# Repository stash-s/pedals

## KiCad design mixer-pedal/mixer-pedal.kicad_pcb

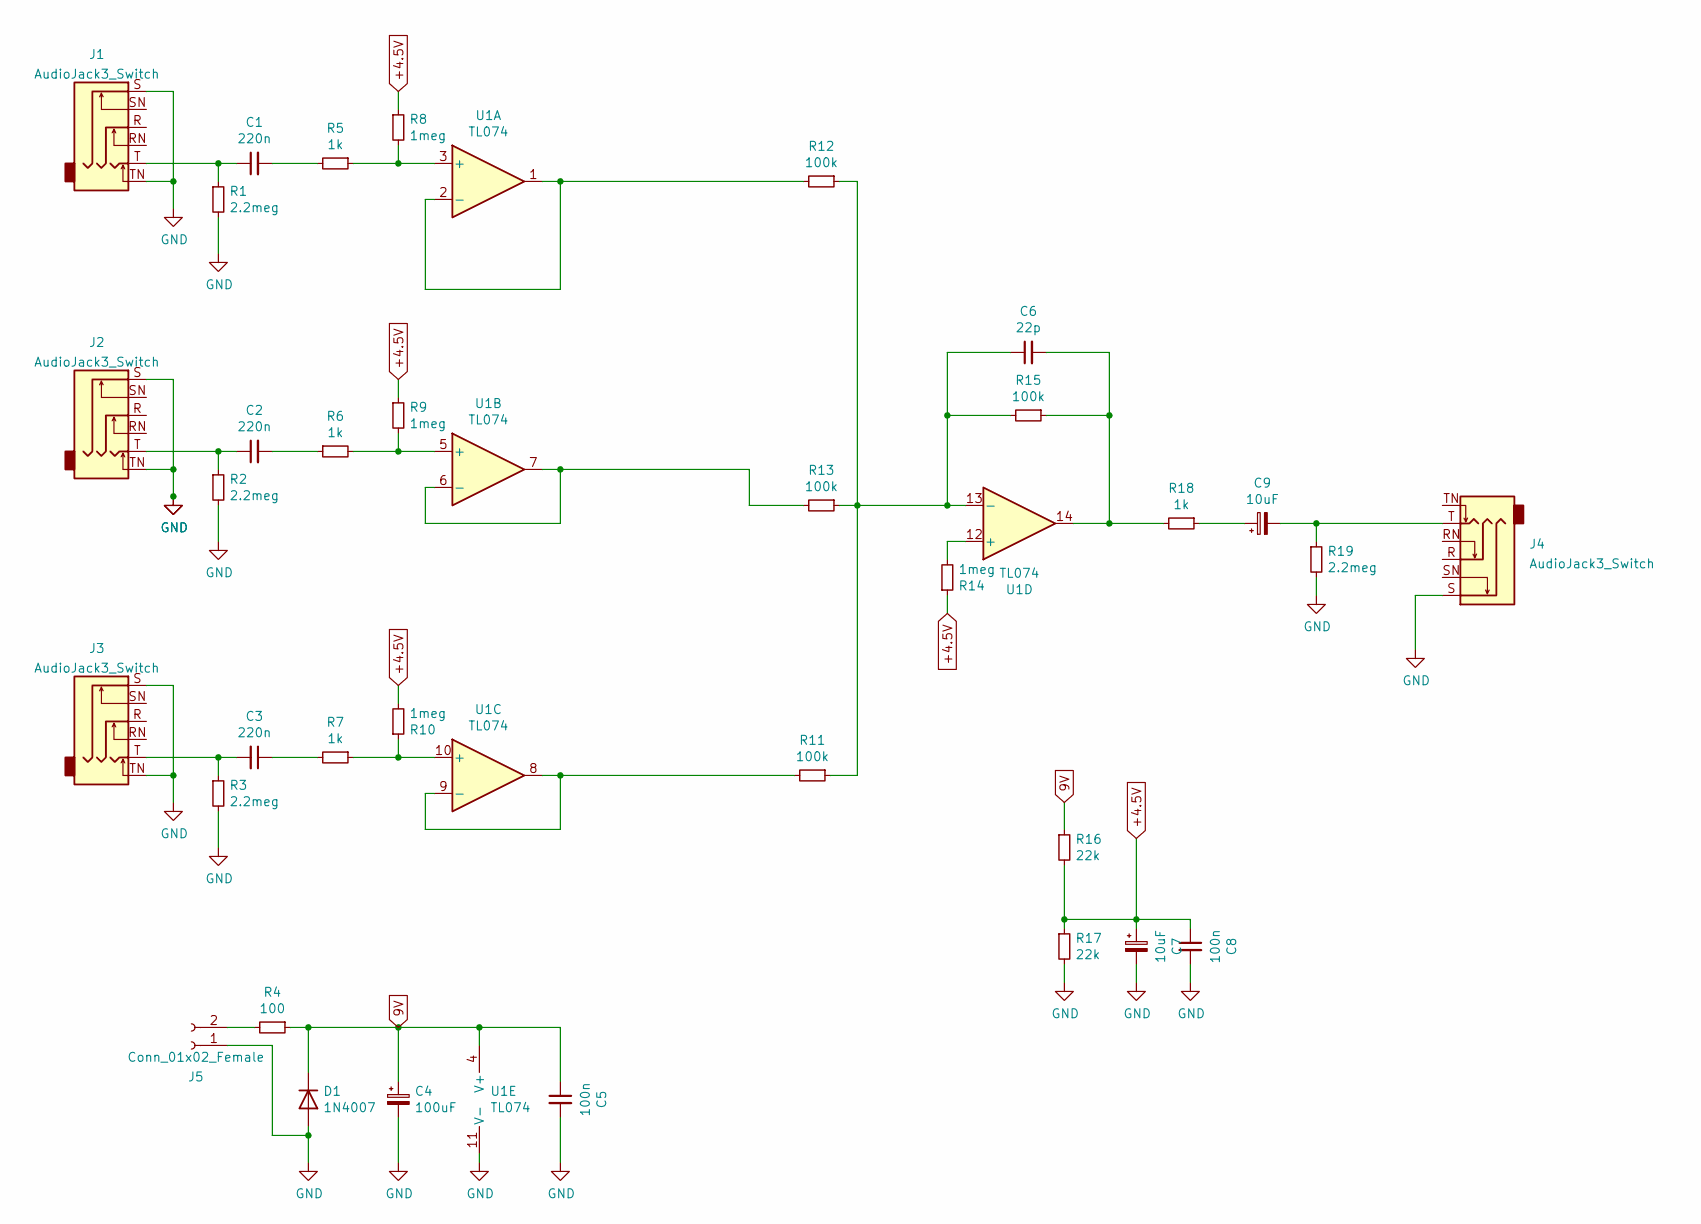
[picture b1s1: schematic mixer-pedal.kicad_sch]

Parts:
C1, C2, C3: 220n; C_Rect_L7.0mm_W2.5mm_P5.00mm
C4: 100uF; CP_Radial_D10.0mm_P5.00mm
C5, C8: 100n; C_Rect_L7.0mm_W2.5mm_P5.00mm
C6: 22p; C_Rect_L7.0mm_W2.5mm_P5.00mm
C7, C9: 10uF; CP_Radial_D10.0mm_P5.00mm
D1: 1N4007; D_DO-41_SOD81_P10.16mm_Horizontal
J1, J2, J3, J4: AudioJack3_Switch; Jack_6.35mm_Rean_NYS215_Horizontal
J5: Conn_01x02_Female; SolderWire-0.5sqmm_1x02_P4.6mm_D0.9mm_OD2.1mm_Relief
R1, R2, R3, R19: 2.2meg; R_Axial_DIN0207_L6.3mm_D2.5mm_P7.62mm_Horizontal
R4: 100; R_Axial_DIN0207_L6.3mm_D2.5mm_P7.62mm_Horizontal
R5, R6, R7, R18: 1k; R_Axial_DIN0207_L6.3mm_D2.5mm_P7.62mm_Horizontal
R8, R9, R10, R14: 1meg; R_Axial_DIN0207_L6.3mm_D2.5mm_P7.62mm_Horizontal
R11, R12, R13, R15: 100k; R_Axial_DIN0207_L6.3mm_D2.5mm_P7.62mm_Horizontal
R16, R17: 22k; R_Axial_DIN0207_L6.3mm_D2.5mm_P7.62mm_Horizontal
U1: TL074; DIP-14_W7.62mm_Socket_LongPads

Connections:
9V: C4.1, C5.1, D1.1 (K), R4.1, R16.1, U1.4 (V+)
+4.5V: C7.1, C8.1, R8.1, R9.1, R10.2, R14.1, R16.2, R17.1
GND: C4.2, C5.2, C7.2, C8.2, D1.2 (A), J1.S, J1.TN, J2.S, J2.TN, J3.S, J3.TN, J4.S, J5.1, R1.2, R2.2, R3.2, R17.2, R19.2, U1.11 (V-)
unnamed: C1.1, J1.T, R1.1
unnamed: C1.2, R5.2
unnamed: C2.1, J2.T, R2.1
unnamed: C2.2, R6.1
unnamed: C3.1, R7.2
unnamed: C3.2, J3.T, R3.1
unnamed: C6.1, R11.1, R12.1, R13.1, R15.2, U1.13 (-)
unnamed: C6.2, R15.1, R18.2, U1.14
unnamed: C9.1, R18.1
unnamed: C9.2, J4.T, R19.1
unnamed: J5.2, R4.2
unnamed: R5.1, R8.2, U1.3 (+)
unnamed: R6.2, R9.2, U1.5 (+)
unnamed: R7.1, R10.1, U1.10 (+)
unnamed: R11.2, U1.8, U1.9 (-)
unnamed: R12.2, U1.1, U1.2 (-)
unnamed: R13.2, U1.6 (-), U1.7
unnamed: R14.2, U1.12 (+)

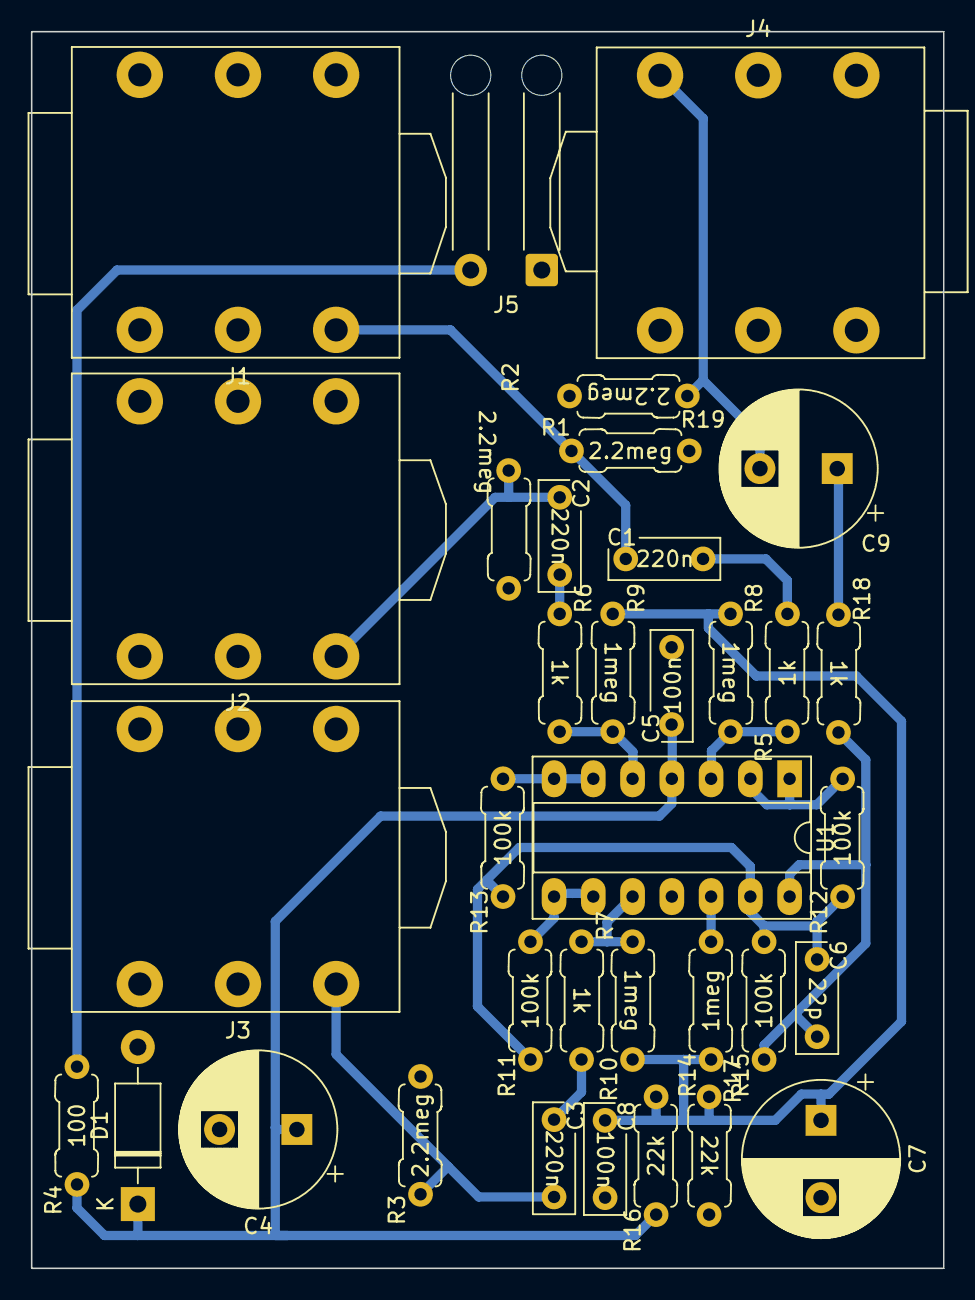
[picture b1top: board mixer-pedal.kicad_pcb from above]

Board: 2 copper layers, 59.0 x 80.0 mm, 35 parts (0 on the bottom side), 21 nets.

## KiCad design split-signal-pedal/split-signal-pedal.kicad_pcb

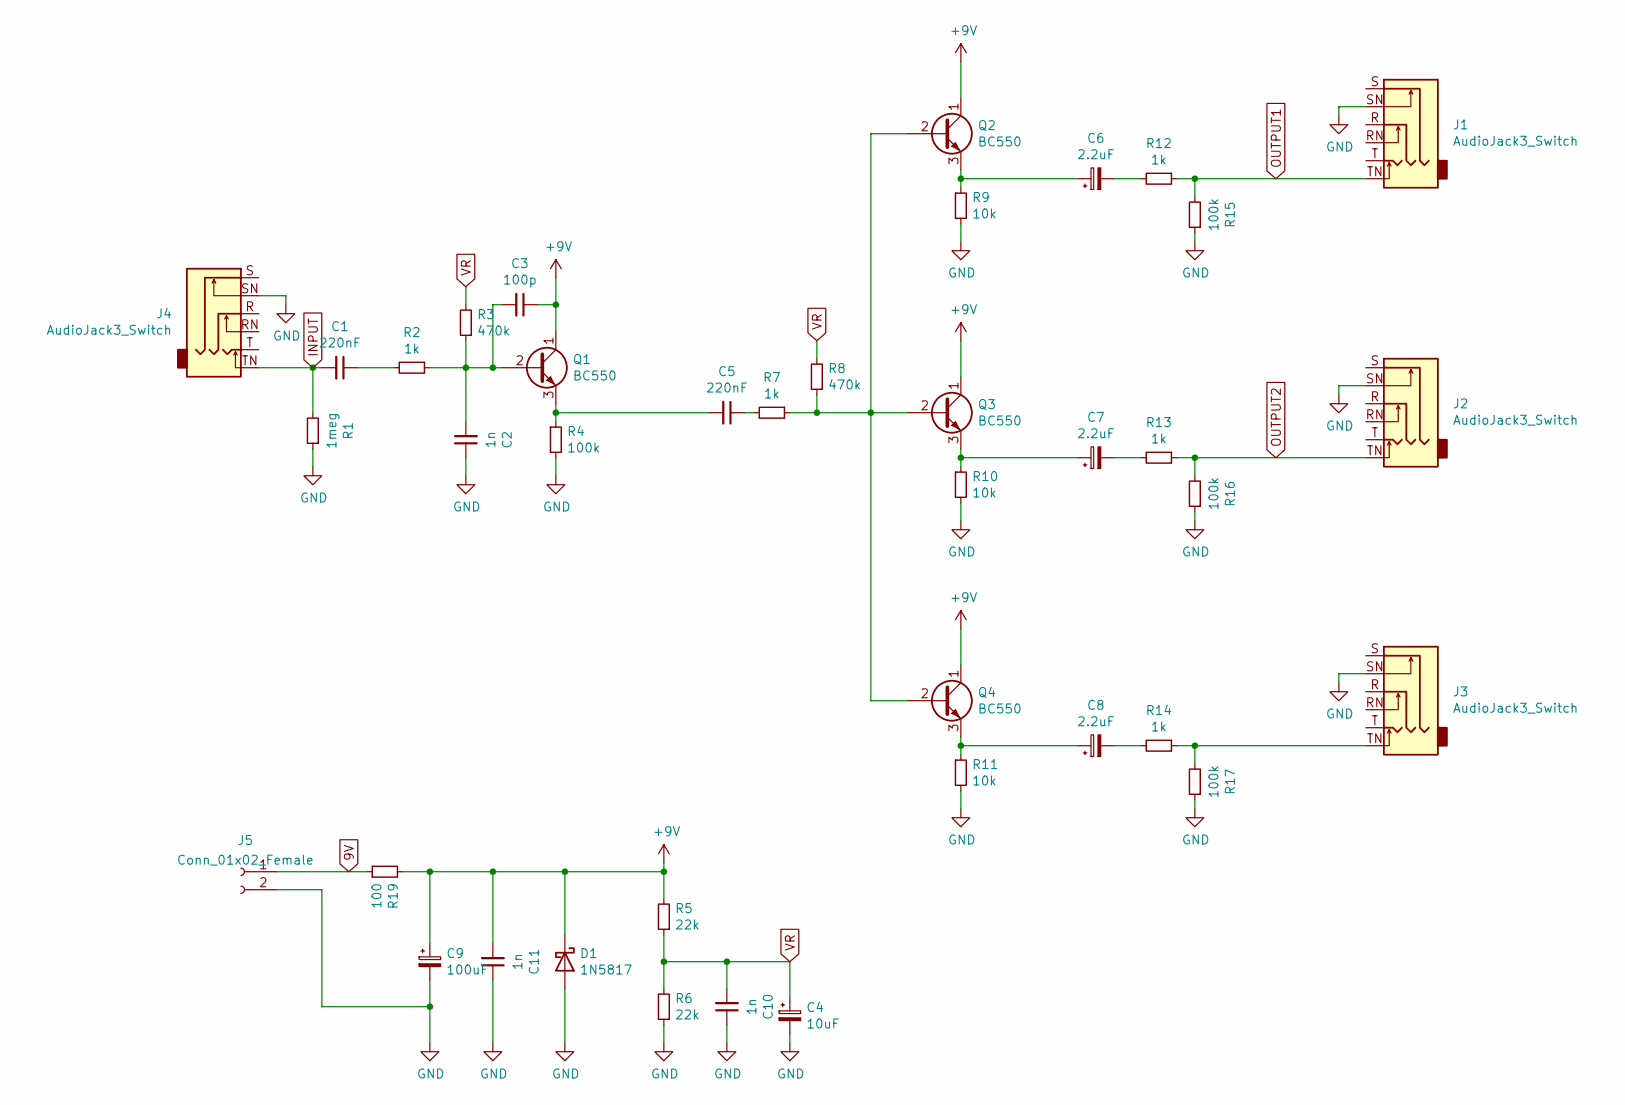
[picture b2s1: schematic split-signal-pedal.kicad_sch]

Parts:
C1, C5: 220nF; C_Rect_L7.0mm_W2.5mm_P5.00mm
C2, C10, C11: 1n; C_Rect_L7.0mm_W2.5mm_P5.00mm
C3: 100p; C_Rect_L7.0mm_W2.5mm_P5.00mm
C4: 10uF; CP_Radial_D5.0mm_P2.50mm
C6, C7, C8: 2.2uF; CP_Radial_D5.0mm_P2.50mm
C9: 100uF; CP_Radial_D10.0mm_P5.00mm
D1: 1N5817; D_DO-41_SOD81_P10.16mm_Horizontal
J1, J2, J3, J4: AudioJack3_Switch; Jack_6.35mm_Rean_NYS215_Horizontal
J5: Conn_01x02_Female; SolderWire-0.1sqmm_1x02_P3.6mm_D0.4mm_OD1mm_Relief
Q1, Q2, Q3, Q4: BC550; TO-92_Inline_Wide
R1: 1meg; R_Axial_DIN0207_L6.3mm_D2.5mm_P7.62mm_Horizontal
R2, R7, R12, R13, R14: 1k; R_Axial_DIN0207_L6.3mm_D2.5mm_P7.62mm_Horizontal
R3, R8: 470k; R_Axial_DIN0207_L6.3mm_D2.5mm_P7.62mm_Horizontal
R4, R15, R16, R17: 100k; R_Axial_DIN0207_L6.3mm_D2.5mm_P7.62mm_Horizontal
R5, R6: 22k; R_Axial_DIN0207_L6.3mm_D2.5mm_P7.62mm_Horizontal
R9, R10, R11: 10k; R_Axial_DIN0207_L6.3mm_D2.5mm_P7.62mm_Horizontal
R19: 100; R_Axial_DIN0207_L6.3mm_D2.5mm_P7.62mm_Horizontal

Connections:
9V: J5.1, R19.1
+9V: C3.1, C9.1, C11.2, D1.1 (K), Q1.1 (C), Q2.1 (C), Q3.1 (C), Q4.1 (C), R5.2, R19.2
GND: C2.1, C4.2, C9.2, C10.1, C11.1, D1.2 (A), J1.SN, J2.SN, J3.SN, J4.SN, J5.2, R1.1, R4.2, R6.1, R9.2, R10.2, R11.2, R15.1, R16.1, R17.1
INPUT: C1.2, J4.TN, R1.2
unnamed: C1.1, R2.2
unnamed: C2.2, C3.2, Q1.2 (B), R2.1, R3.1
unnamed: C5.1, R7.2
unnamed: C5.2, Q1.3 (E), R4.1
unnamed: C6.1, Q2.3 (E), R9.1
unnamed: C6.2, R12.2
unnamed: C7.1, Q3.3 (E), R10.1
unnamed: C7.2, R13.2
unnamed: C8.1, Q4.3 (E), R11.1
unnamed: C8.2, R14.2
unnamed: Q2.2 (B), Q3.2 (B), Q4.2 (B), R7.1, R8.1
unnamed: J3.TN, R14.1, R17.2
OUTPUT1: J1.TN, R12.1, R15.2
OUTPUT2: J2.TN, R13.1, R16.2
VR: C4.1, C10.2, R3.2, R5.1, R6.2, R8.2

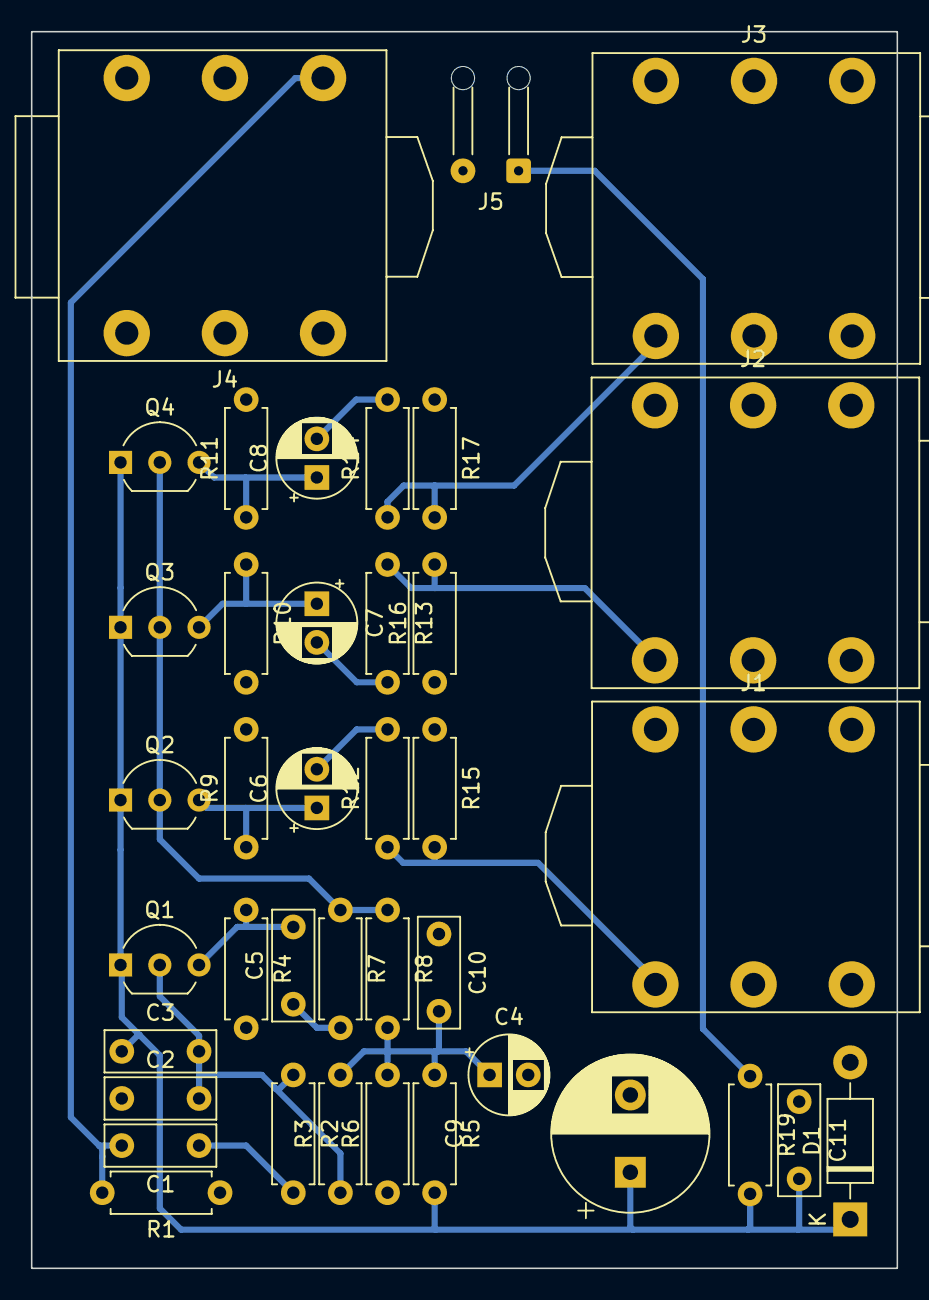
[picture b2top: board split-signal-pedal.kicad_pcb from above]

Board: 2 copper layers, 56.0 x 80.0 mm, 39 parts (0 on the bottom side), 19 nets.

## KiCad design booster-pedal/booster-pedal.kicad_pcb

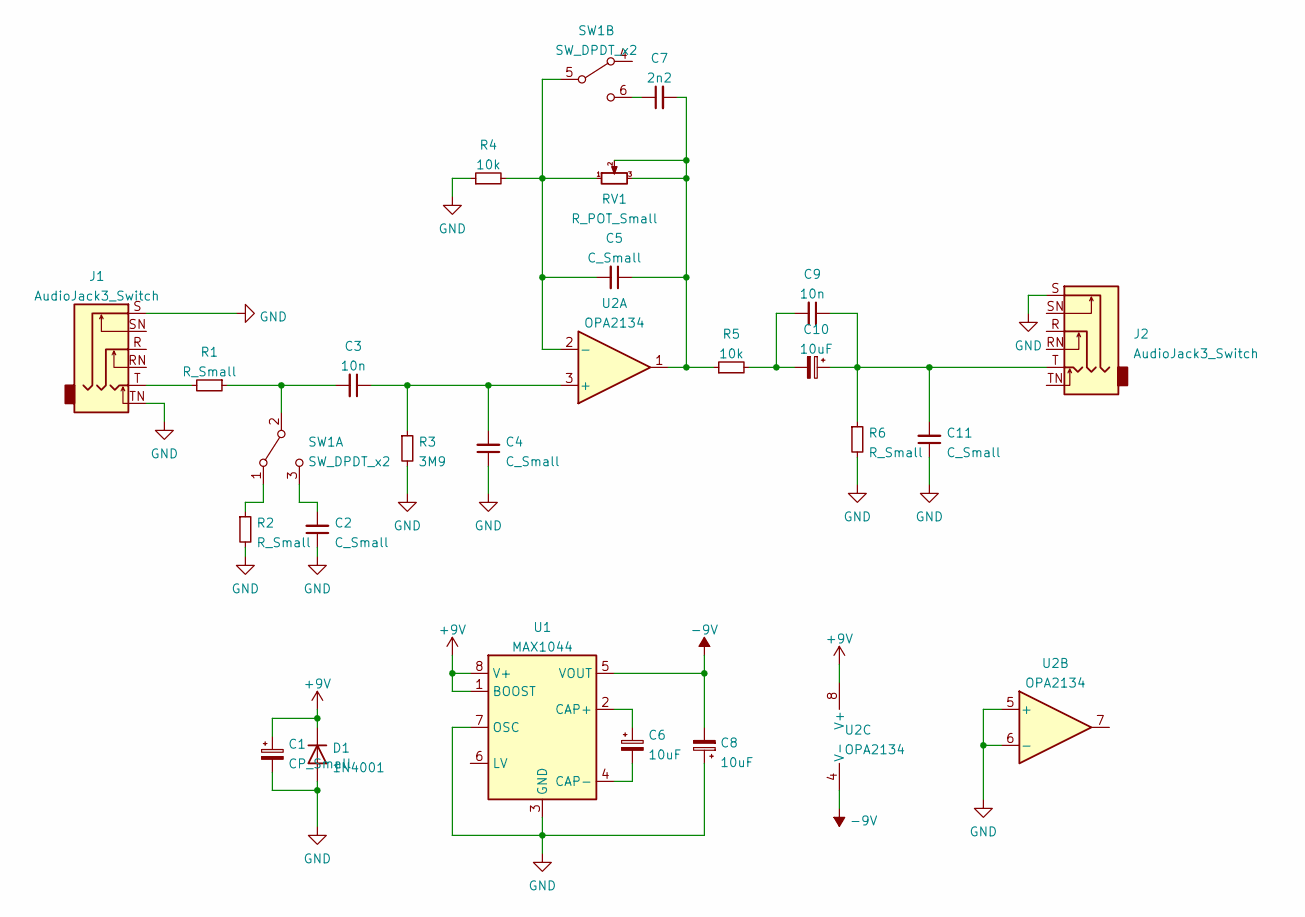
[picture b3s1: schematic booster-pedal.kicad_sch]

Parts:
C1: CP_Small; CP_Radial_D5.0mm_P2.50mm
C2, C4, C5, C11: C_Small; C_Disc_D4.7mm_W2.5mm_P5.00mm
C3, C9: 10n; C_Disc_D4.7mm_W2.5mm_P5.00mm
C6, C8, C10: 10uF; CP_Radial_D5.0mm_P2.50mm
C7: 2n2; C_Disc_D4.7mm_W2.5mm_P5.00mm
D1: 1N4001; D_DO-41_SOD81_P10.16mm_Horizontal
J1, J2: AudioJack3_Switch; Jack_6.35mm_Rean_NYS215_Horizontal
R1, R2, R6: R_Small; R_Axial_DIN0207_L6.3mm_D2.5mm_P7.62mm_Horizontal
R3: 3M9; R_Axial_DIN0207_L6.3mm_D2.5mm_P7.62mm_Horizontal
R4, R5: 10k; R_Axial_DIN0207_L6.3mm_D2.5mm_P7.62mm_Horizontal
RV1: R_POT_Small; Potentiometer_Alpha_RD901F-40-00D_Single_Vertical
SW1: SW_DPDT_x2; SW_E-Switch_EG1271_DPDT
U1: MAX1044; DIP-8_W7.62mm_Socket_LongPads
U2: OPA2134; DIP-8_W7.62mm_Socket_LongPads

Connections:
+9V: C1.1, D1.1 (K), U1.1 (BOOST), U1.8 (V+), U2.8 (V+)
-9V: C8.2, U1.5 (VOUT), U2.4 (V-)
GND: C1.2, C2.1, C4.1, C8.1, C11.1, D1.2 (A), J1.S, J1.TN, J2.S, R2.2, R3.2, R4.1, R6.2, U1.3 (GND), U1.7 (OSC), U2.5 (+), U2.6 (-)
unnamed: C2.2, SW1.3 (C)
unnamed: C3.1, C4.2, R3.1, U2.3 (+)
unnamed: C3.2, R1.1, SW1.2 (B)
unnamed: C6.1, U1.2 (CAP+)
unnamed: C6.2, U1.4 (CAP-)
unnamed: C7.1, SW1.6 (C)
unnamed: C5.1, C7.2, R5.1, RV1.2, RV1.3, U2.1
unnamed: C9.1, C10.1, C11.2, J2.T, R6.1
unnamed: C9.2, C10.2, R5.2
unnamed: J1.T, R1.2
unnamed: R2.1, SW1.1 (A)
unnamed: C5.2, R4.2, RV1.1, SW1.5 (B), U2.2 (-)

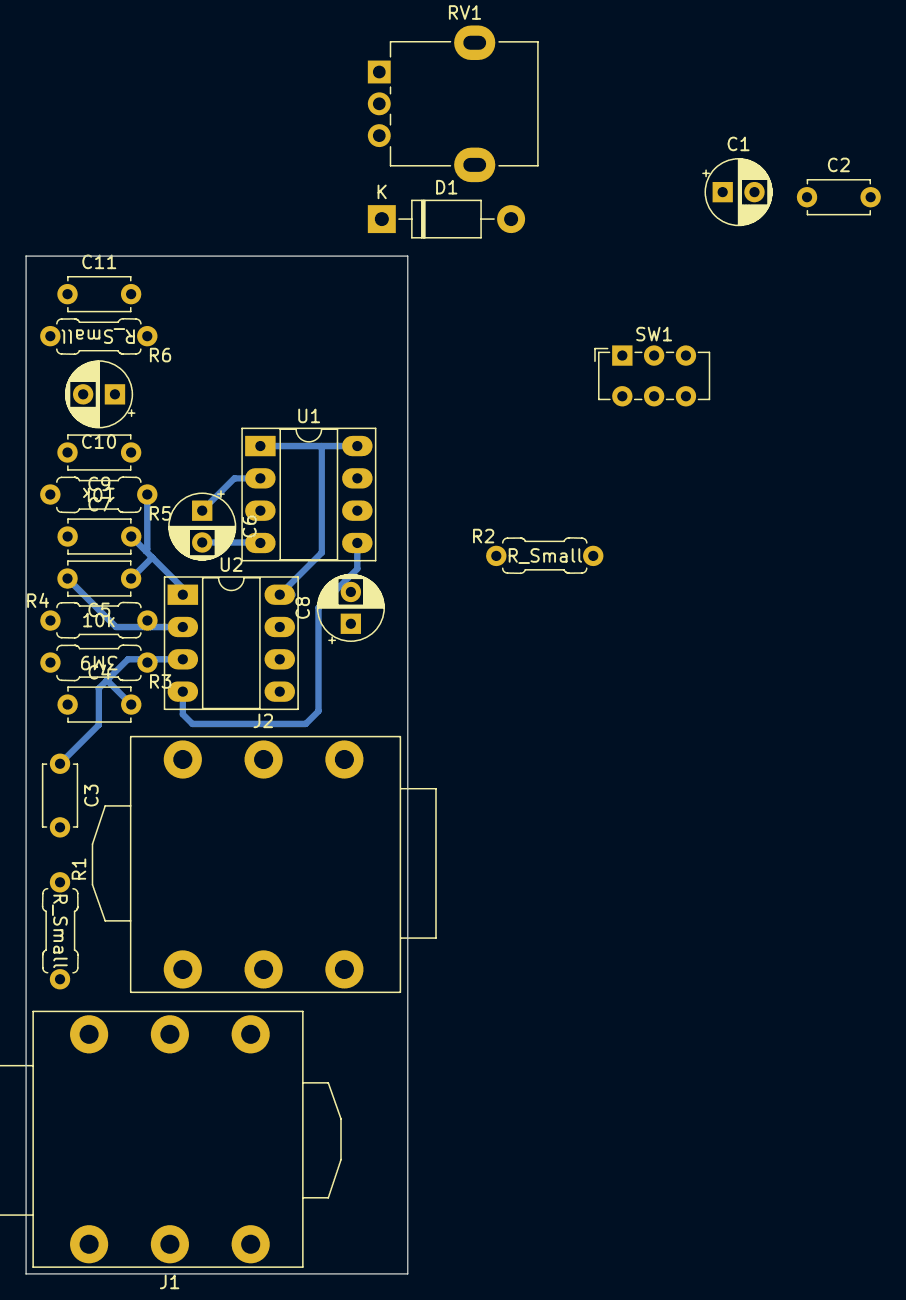
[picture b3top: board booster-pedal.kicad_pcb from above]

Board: 2 copper layers, 30.0 x 80.0 mm, 24 parts (0 on the bottom side), 15 nets.

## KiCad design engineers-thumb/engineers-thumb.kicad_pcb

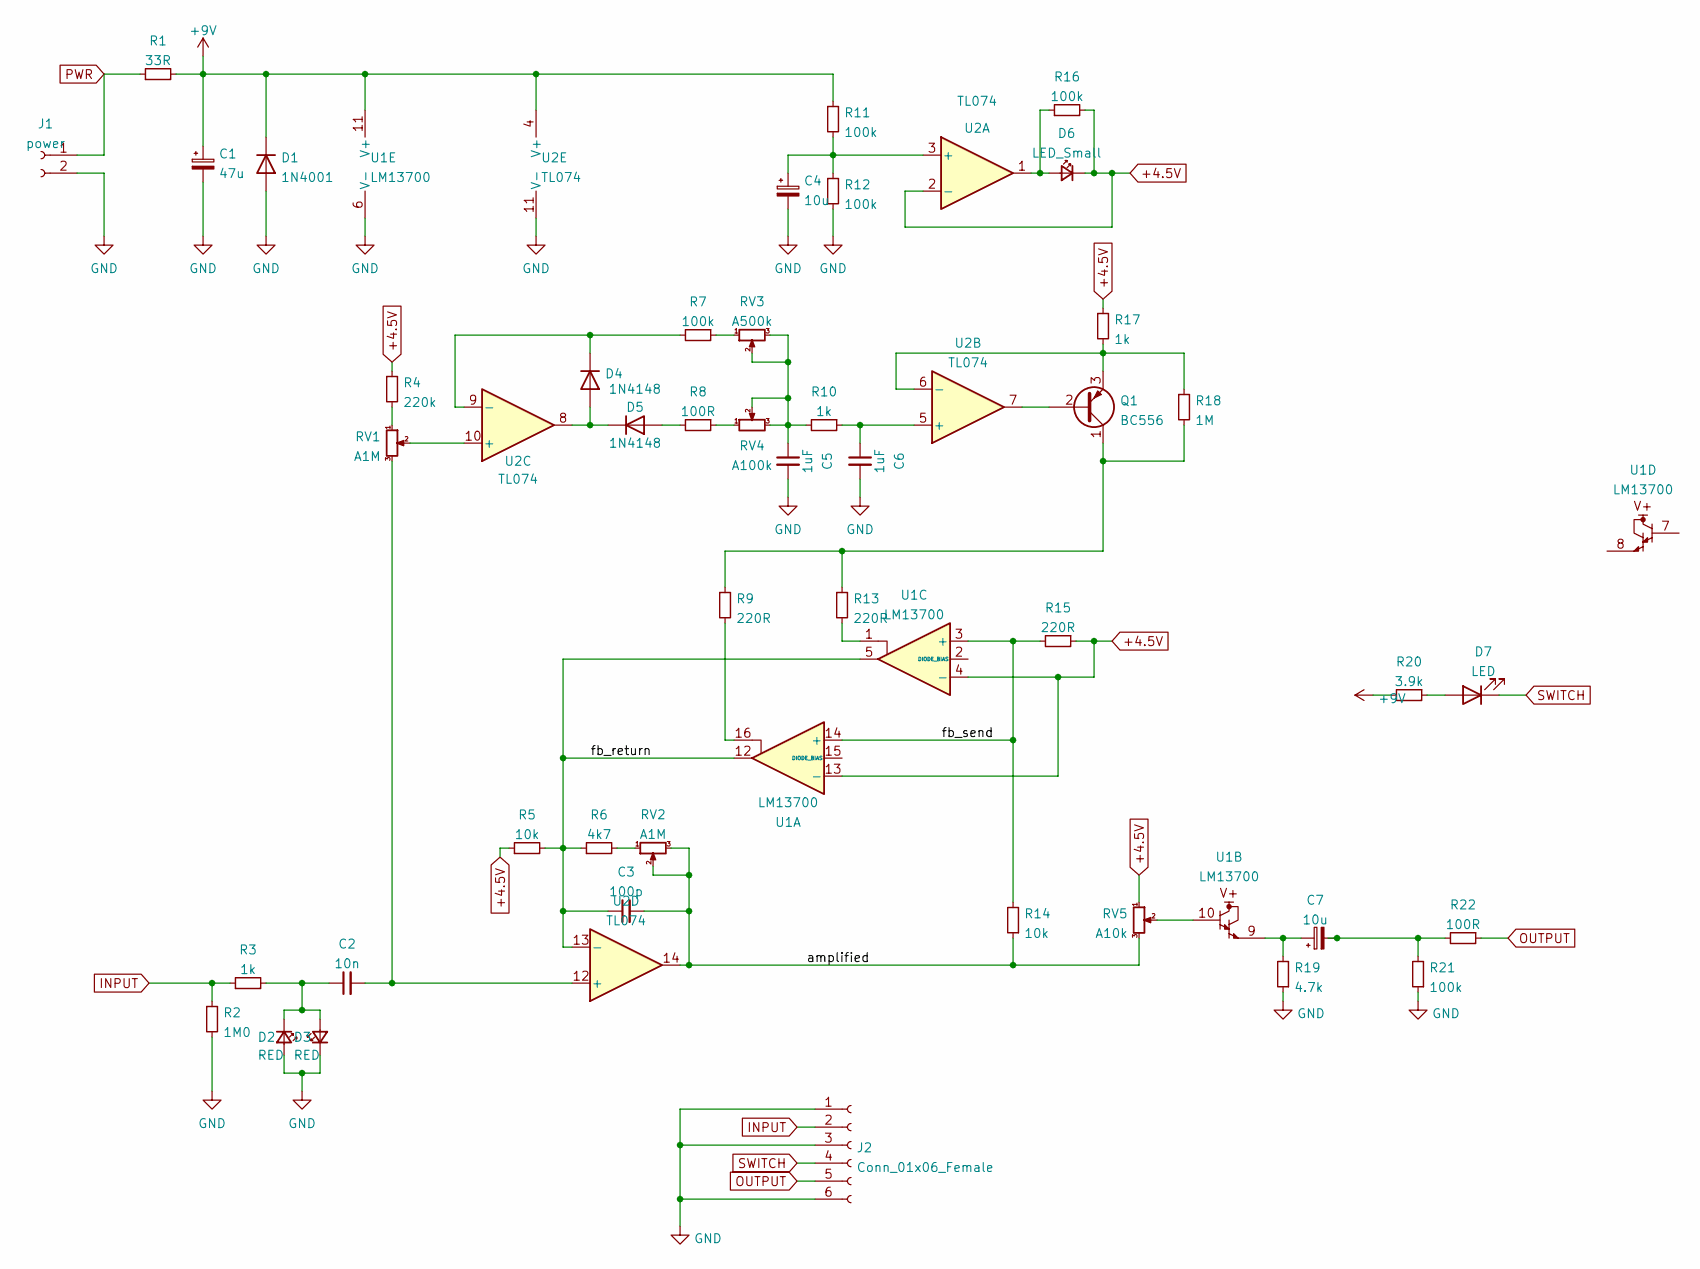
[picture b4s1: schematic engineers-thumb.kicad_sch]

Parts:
C1: 47u; CP_Radial_D8.0mm_P3.50mm
C2: 10n; C_Rect_L7.0mm_W2.5mm_P5.00mm
C3: 100p; C_Disc_D5.0mm_W2.5mm_P2.50mm
C4, C7: 10u; CP_Radial_D5.0mm_P2.50mm
C5, C6: 1uF; C_Rect_L7.0mm_W2.5mm_P5.00mm
D1: 1N4001; D_DO-41_SOD81_P10.16mm_Horizontal
D2, D3: RED; LED_D3.0mm
D4, D5: 1N4148; D_DO-35_SOD27_P7.62mm_Horizontal
D6: LED_Small; LED_D3.0mm_Clear
D7: LED; LED_D3.0mm
J1: power; SolderWire-0.1sqmm_1x02_P3.6mm_D0.4mm_OD1mm
J2: Conn_01x06_Female; SolderWire-0.1sqmm_1x06_P3.6mm_D0.4mm_OD1mm
Q1: BC556; TO-92_Inline_Wide
R1: 33R; R_Axial_DIN0207_L6.3mm_D2.5mm_P7.62mm_Horizontal
R2: 1M0; R_Axial_DIN0207_L6.3mm_D2.5mm_P7.62mm_Horizontal
R3, R10, R17: 1k; R_Axial_DIN0207_L6.3mm_D2.5mm_P7.62mm_Horizontal
R4: 220k; R_Axial_DIN0207_L6.3mm_D2.5mm_P7.62mm_Horizontal
R5, R14: 10k; R_Axial_DIN0207_L6.3mm_D2.5mm_P7.62mm_Horizontal
R6: 4k7; R_Axial_DIN0207_L6.3mm_D2.5mm_P7.62mm_Horizontal
R7, R11, R12, R16, R21: 100k; R_Axial_DIN0207_L6.3mm_D2.5mm_P7.62mm_Horizontal
R8, R22: 100R; R_Axial_DIN0207_L6.3mm_D2.5mm_P7.62mm_Horizontal
R9, R13, R15: 220R; R_Axial_DIN0207_L6.3mm_D2.5mm_P7.62mm_Horizontal
R18: 1M; R_Axial_DIN0207_L6.3mm_D2.5mm_P7.62mm_Horizontal
R19: 4.7k; R_Axial_DIN0207_L6.3mm_D2.5mm_P7.62mm_Horizontal
R20: 3.9k; R_Axial_DIN0207_L6.3mm_D2.5mm_P7.62mm_Horizontal
RV1, RV2: A1M; PinHeader_1x03_P2.54mm_Vertical
RV3: A500k; PinHeader_1x03_P2.54mm_Vertical
RV4: A100k; PinHeader_1x03_P2.54mm_Vertical
RV5: A10k; SolderWire-0.1sqmm_1x03_P3.6mm_D0.4mm_OD1mm
U1: LM13700; DIP-16_W7.62mm_LongPads
U2: TL074; DIP-14_W7.62mm_Socket_LongPads

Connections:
+4.5V: D6.1 (K), R4.1, R5.1, R15.1, R16.2, R17.1, RV5.1, U1.4 (-), U1.13 (-), U2.2 (-)
+9V: C1.1, D1.1 (K), R1.2, R11.1, R20.2, U1.11 (V+), U2.4 (V+)
/amplified: C3.2, R14.1, RV2.2, RV2.3, RV5.3, U2.14
/fb_return: C3.1, R5.2, R6.1, U1.5, U1.12, U2.13 (-)
/fb_send: R14.2, R15.2, U1.3 (+), U1.14 (+)
GND: C1.2, C4.2, C5.2, C6.2, D1.2 (A), D2.2 (A), D3.1 (K), J1.2, J2.1, J2.3, J2.6, R2.2, R12.2, R19.1, R21.1, U1.6 (V-), U2.11 (V-)
INPUT: J2.2, R2.1, R3.1
unnamed: C2.1, D2.1 (K), D3.2 (A), R3.2
unnamed: C2.2, RV1.3, U2.12 (+)
unnamed: C4.1, R11.2, R12.1, U2.3 (+)
unnamed: C5.1, R10.2, RV3.2, RV3.3, RV4.2, RV4.3
unnamed: C6.1, R10.1, U2.5 (+)
unnamed: C7.1, R19.2, U1.9
unnamed: C7.2, R21.2, R22.2
unnamed: D4.1 (K), R7.2, U2.9 (-)
unnamed: D4.2 (A), D5.1 (K), U2.8
unnamed: D5.2 (A), R8.2
unnamed: D6.2 (A), R16.1, U2.1
unnamed: D7.2 (A), R20.1
unnamed: Q1.1 (C), R9.1, R13.1, R18.2
unnamed: Q1.2 (B), U2.7
unnamed: Q1.3 (E), R17.2, R18.1, U2.6 (-)
unnamed: R4.2, RV1.1
unnamed: R6.2, RV2.1
unnamed: R7.1, RV3.1
unnamed: R8.1, RV4.1
unnamed: R9.2, U1.16
unnamed: R13.2, U1.1
unnamed: RV1.2, U2.10 (+)
unnamed: RV5.2, U1.10
OUTPUT: J2.5, R22.1
PWR: J1.1, R1.1
SWITCH: D7.1 (K), J2.4

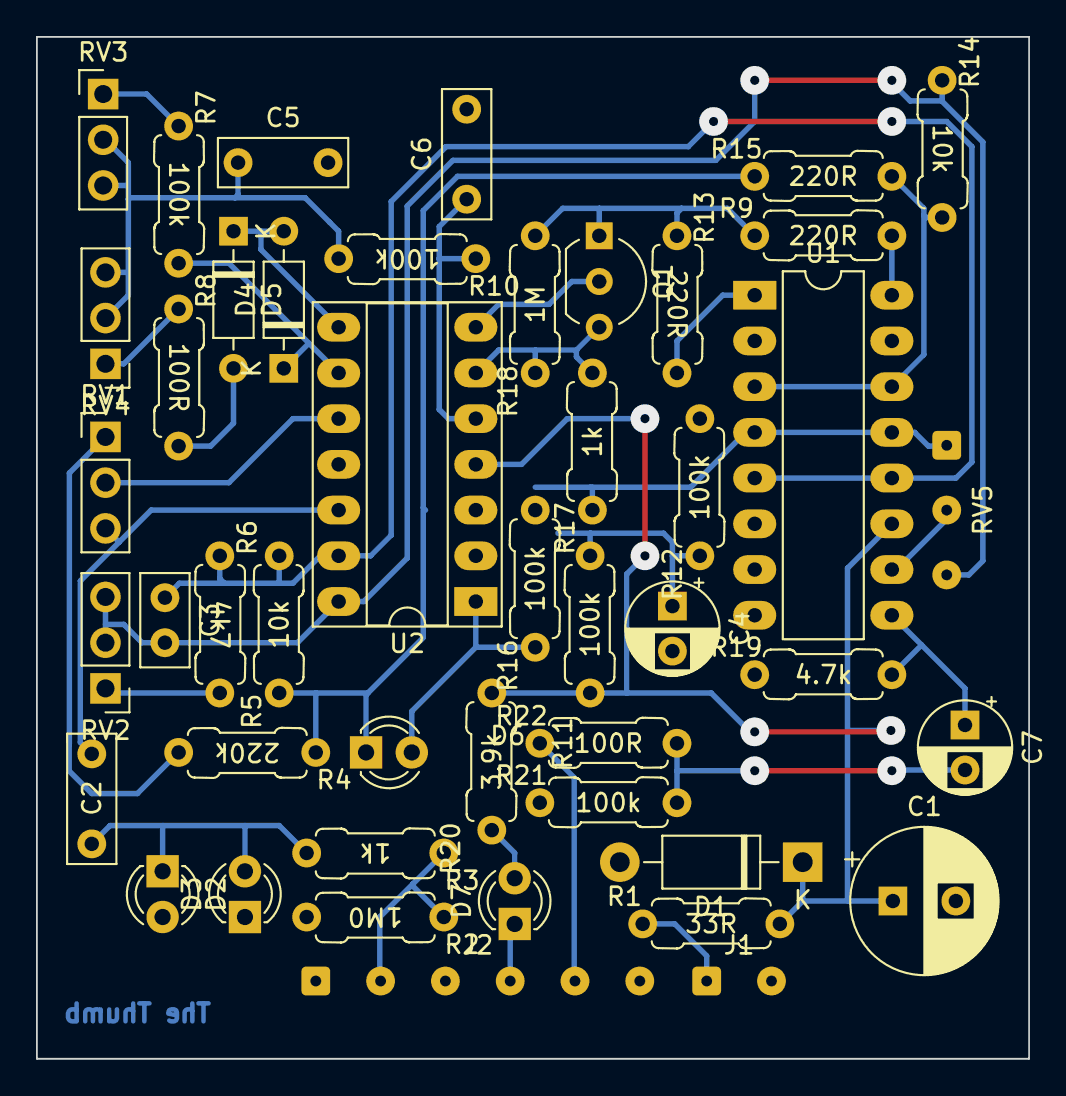
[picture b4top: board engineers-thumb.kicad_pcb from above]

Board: 2 copper layers, 55.1 x 56.8 mm, 46 parts (0 on the bottom side), 33 nets.

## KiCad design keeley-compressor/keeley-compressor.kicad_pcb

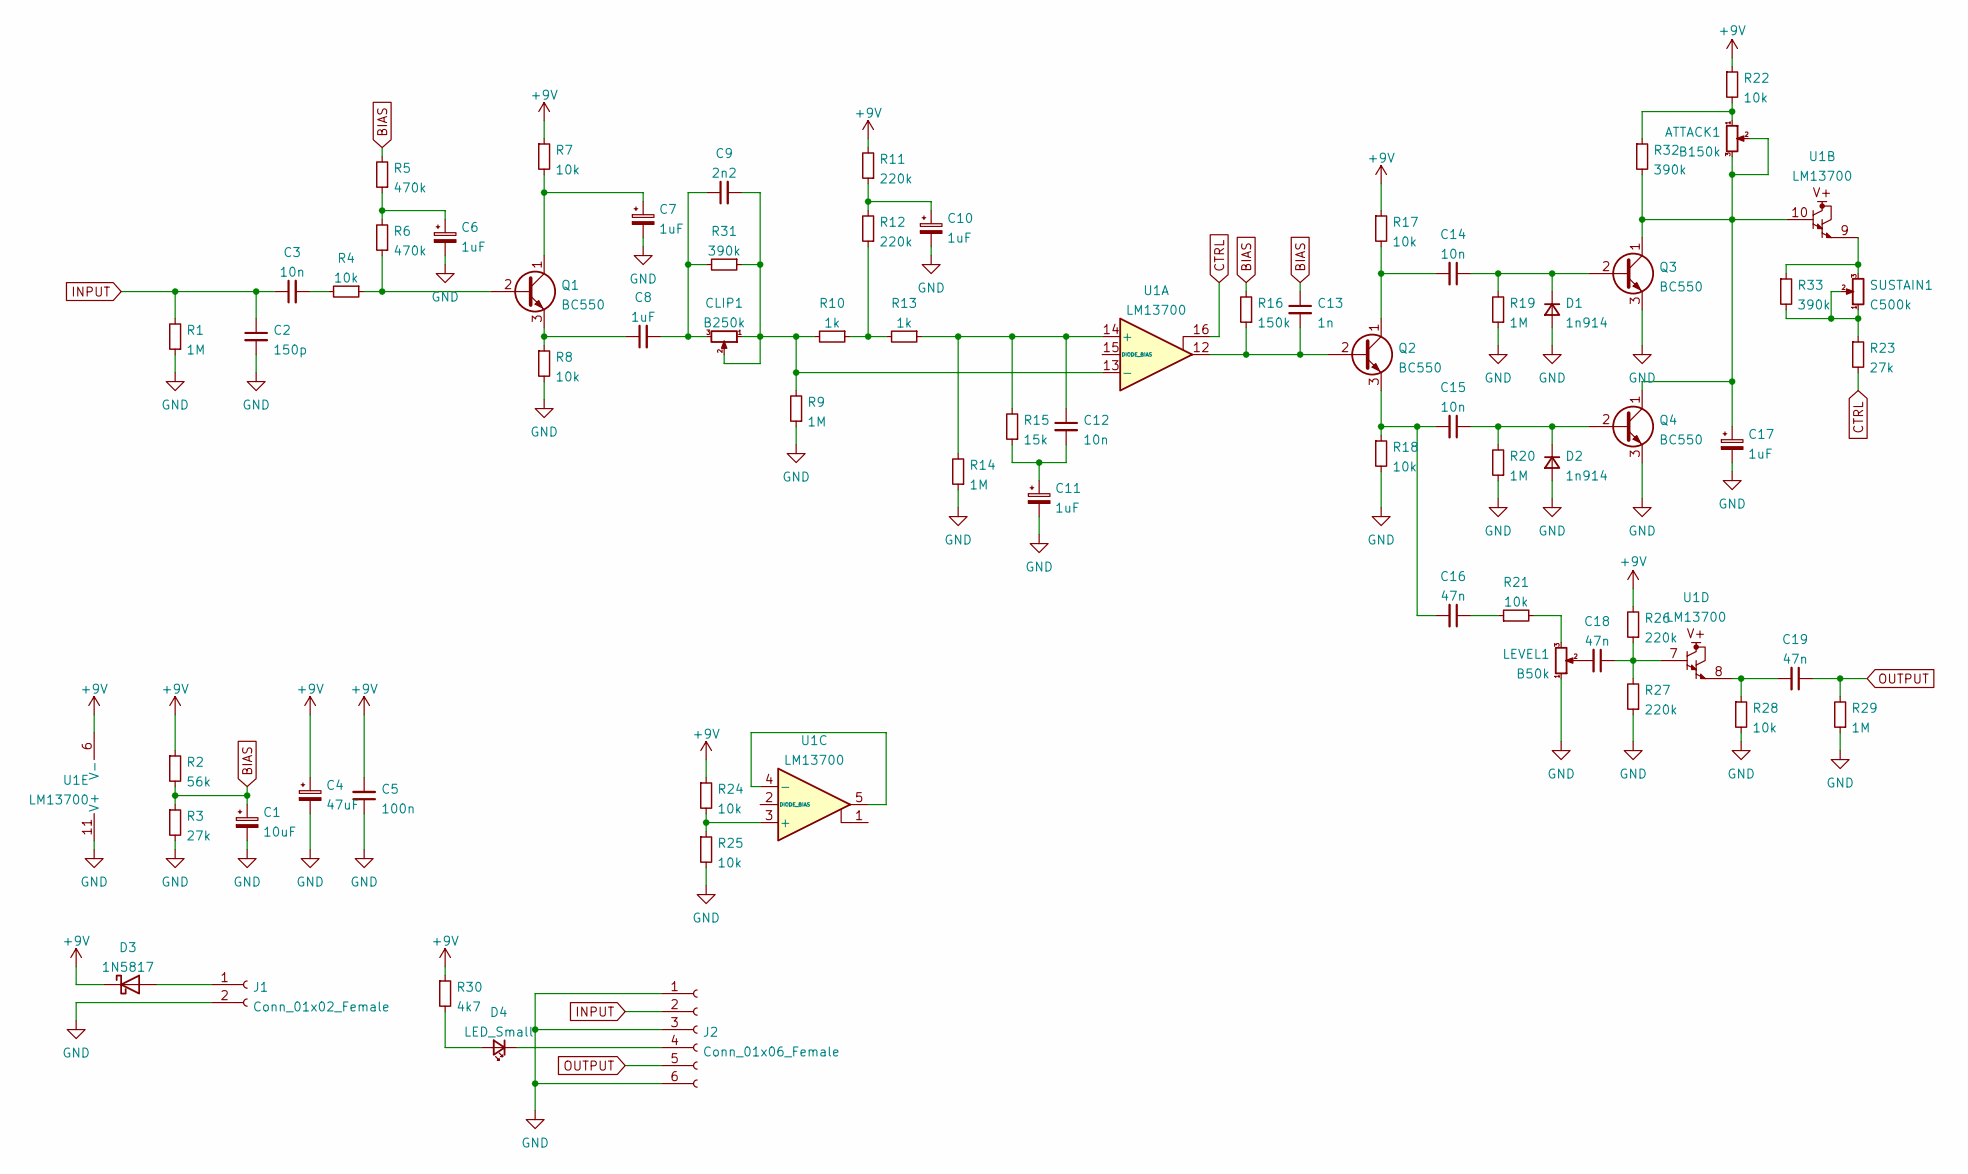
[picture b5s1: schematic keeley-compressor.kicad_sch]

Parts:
ATTACK1: B150k; RV16AF-41
C1: 10uF; CP_Radial_D5.0mm_P2.50mm
C2: 150p; C_Rect_L7.0mm_W2.5mm_P5.00mm
C3, C12, C14, C15: 10n; C_Rect_L7.0mm_W2.5mm_P5.00mm
C4: 47uF; CP_Radial_D5.0mm_P2.50mm
C5: 100n; C_Rect_L7.0mm_W2.5mm_P5.00mm
C6, C7, C10, C11, C17: 1uF; CP_Radial_D5.0mm_P2.50mm
C8: 1uF; C_Rect_L7.0mm_W2.5mm_P5.00mm
C9: 2n2; C_Rect_L7.0mm_W2.5mm_P5.00mm
C13: 1n; C_Rect_L7.0mm_W2.5mm_P5.00mm
C16, C18, C19: 47n; C_Rect_L7.0mm_W2.5mm_P5.00mm
CLIP1: B250k; RV16AF-41
D1, D2: 1n914; D_DO-35_SOD27_P7.62mm_Horizontal
D3: 1N5817; D_DO-41_SOD81_P10.16mm_Horizontal
D4: LED_Small; LED_D3.0mm
J1: Conn_01x02_Female; SolderWire-0.1sqmm_1x02_P3.6mm_D0.4mm_OD1mm_Relief
J2: Conn_01x06_Female; SolderWire-0.1sqmm_1x06_P3.6mm_D0.4mm_OD1mm
LEVEL1: B50k; RV16AF-41
Q1, Q2, Q3, Q4: BC550; TO-92_Inline_Wide
R1, R9, R14, R19, R20, R29: 1M; R_Axial_DIN0207_L6.3mm_D2.5mm_P7.62mm_Horizontal
R2: 56k; R_Axial_DIN0207_L6.3mm_D2.5mm_P7.62mm_Horizontal
R3, R23: 27k; R_Axial_DIN0207_L6.3mm_D2.5mm_P7.62mm_Horizontal
R4, R7, R8, R17, R18, R21, R22, R24, R25, R28: 10k; R_Axial_DIN0207_L6.3mm_D2.5mm_P7.62mm_Horizontal
R5, R6: 470k; R_Axial_DIN0207_L6.3mm_D2.5mm_P7.62mm_Horizontal
R10, R13: 1k; R_Axial_DIN0207_L6.3mm_D2.5mm_P7.62mm_Horizontal
R11, R12, R26, R27: 220k; R_Axial_DIN0207_L6.3mm_D2.5mm_P7.62mm_Horizontal
R15: 15k; R_Axial_DIN0207_L6.3mm_D2.5mm_P7.62mm_Horizontal
R16: 150k; R_Axial_DIN0207_L6.3mm_D2.5mm_P7.62mm_Horizontal
R30: 4k7; R_Axial_DIN0207_L6.3mm_D2.5mm_P7.62mm_Horizontal
R31, R32, R33: 390k; R_Axial_DIN0207_L6.3mm_D2.5mm_P7.62mm_Horizontal
SUSTAIN1: C500k; RV16AF-41
U1: LM13700; DIP-16_W7.62mm_Socket_LongPads

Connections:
+9V: C4.1, C5.2, D3.1 (K), R2.1, R7.1, R11.2, R17.1, R22.1, R24.1, R26.2, R30.1, U1.6 (V-)
BIAS: C1.1, C13.1, R2.2, R3.1, R5.2, R16.2
CTRL: R23.2, U1.16
GND: C1.2, C2.2, C4.2, C5.1, C6.2, C7.2, C10.2, C11.2, C17.2, D1.2 (A), D2.2 (A), J1.2, J2.1, J2.3, J2.6, LEVEL1.1, Q3.3 (E), Q4.3 (E), R1.1, R3.2, R8.2, R9.1, R14.1, R18.2, R19.1, R20.1, R25.2, R27.1, R28.2, R29.1, U1.11 (V+)
INPUT: C2.1, C3.1, J2.2, R1.2
unnamed: C3.2, R4.2
unnamed: C6.1, R5.1, R6.2
unnamed: C7.1, Q1.1 (C), R7.2
unnamed: C8.1, Q1.3 (E), R8.1
unnamed: C8.2, C9.1, CLIP1.3, R31.2
unnamed: C9.2, CLIP1.1, CLIP1.2, R9.2, R10.2, R31.1, U1.13 (-)
unnamed: C10.1, R11.1, R12.2
unnamed: C11.1, C12.2, R15.1
unnamed: C12.1, R13.1, R14.2, R15.2, U1.14 (+)
unnamed: C13.2, Q2.2 (B), R16.1, U1.12
unnamed: C14.1, D1.1 (K), Q3.2 (B), R19.2
unnamed: C14.2, Q2.1 (C), R17.2
unnamed: C15.1, D2.1 (K), Q4.2 (B), R20.2
unnamed: C15.2, C16.2, Q2.3 (E), R18.1
unnamed: C16.1, R21.1
unnamed: ATTACK1.2, ATTACK1.3, C17.1, Q3.1 (C), Q4.1 (C), R32.2, U1.10
unnamed: C18.1, R26.1, R27.2, U1.7
unnamed: D3.2 (A), J1.1
unnamed: D4.1 (K), J2.4
unnamed: D4.2 (A), R30.2
unnamed: C18.2, LEVEL1.2
unnamed: Q1.2 (B), R4.1, R6.1
unnamed: R10.1, R12.1, R13.2
unnamed: LEVEL1.3, R21.2
unnamed: ATTACK1.1, R22.2, R32.1
unnamed: R23.1, R33.2, SUSTAIN1.1, SUSTAIN1.2
unnamed: R33.1, SUSTAIN1.3, U1.9
unnamed: R24.2, R25.1, U1.3 (+)
unnamed: U1.4 (-), U1.5
unnamed: C19.2, R28.1, U1.8
OUTPUT: C19.1, J2.5, R29.2
